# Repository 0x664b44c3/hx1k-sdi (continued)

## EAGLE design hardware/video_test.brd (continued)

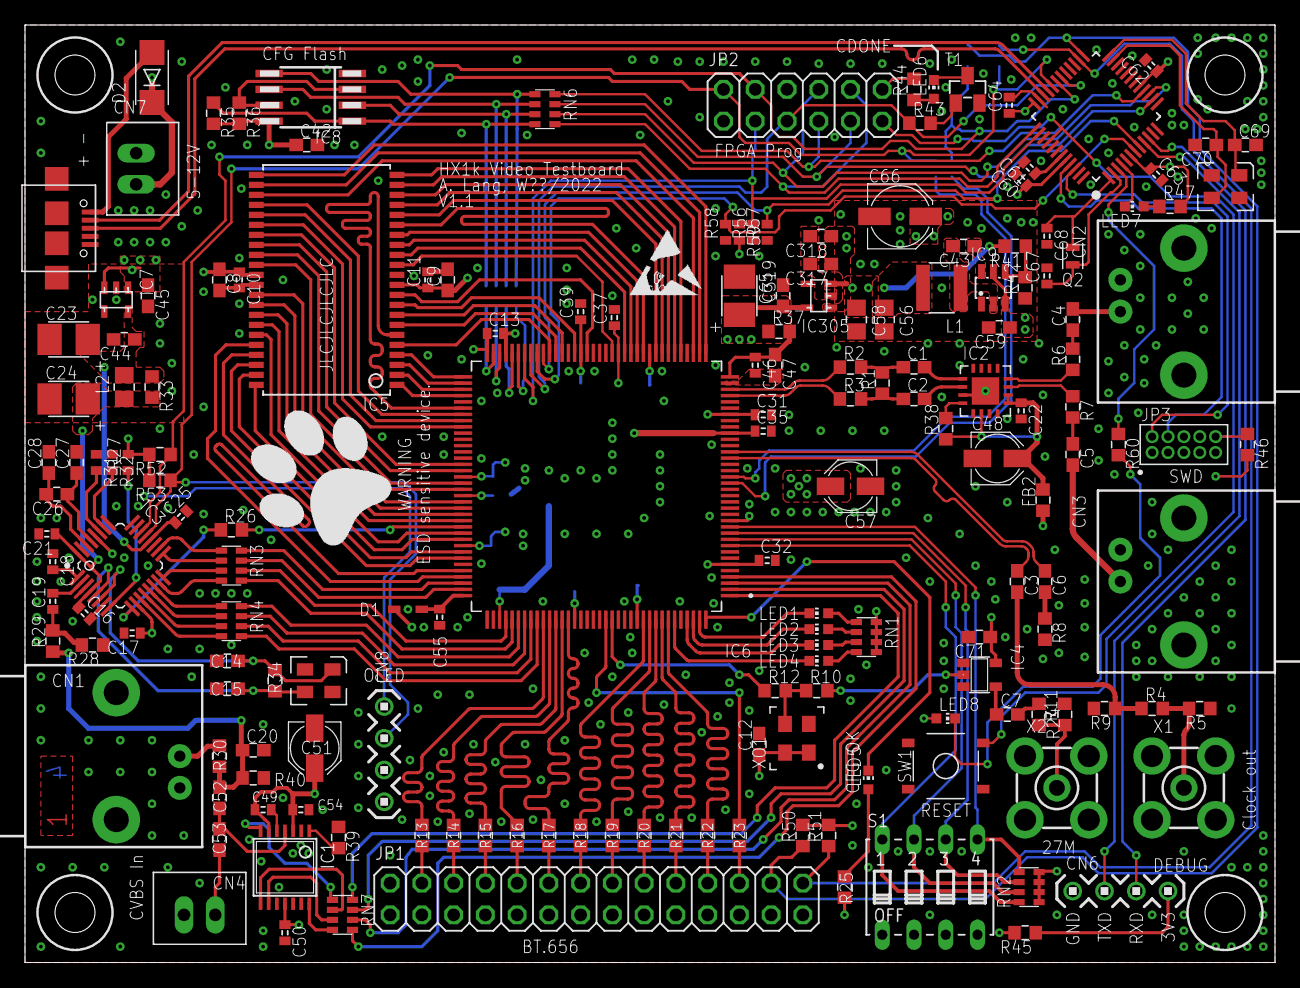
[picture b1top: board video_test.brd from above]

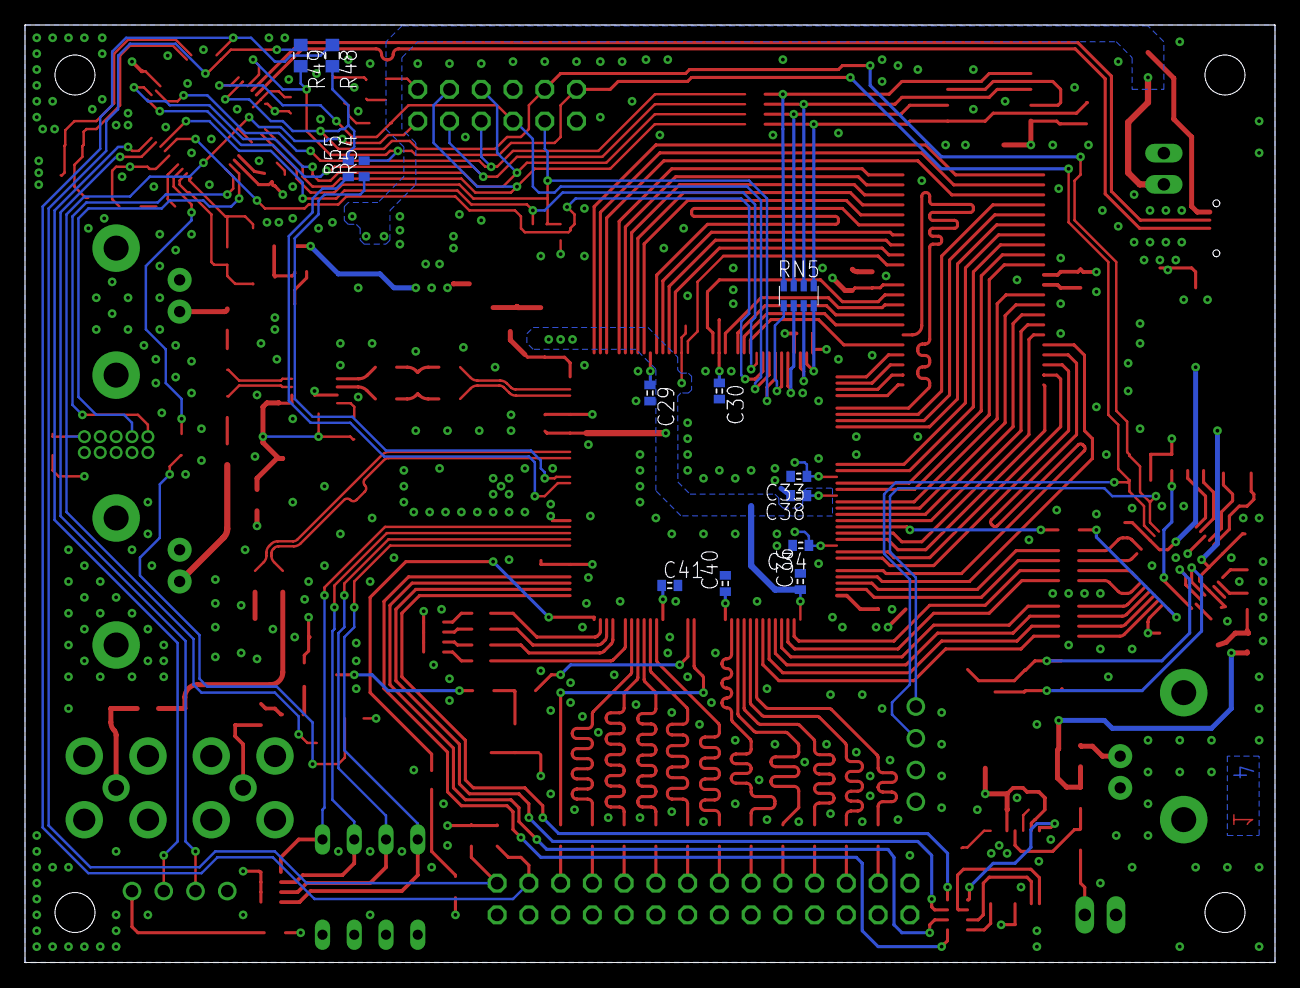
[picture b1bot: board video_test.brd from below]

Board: 4 copper layers, 100.0 x 75.0 mm, 185 parts (13 on the bottom side), 198 nets.

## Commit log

2022-07-05 added hardware source files
2022-07-05 Added schematics pdf and initial fpga bitstream
2022-07-05 added image of the pcb
2022-07-05 Update README.md
    added image
2022-07-05 update schematics pdf (only contained first page)
2022-07-06 added docu images
2022-07-08 better board photo
2022-07-08 Update errata.md
    fixed typo
2022-07-09 Added serializer hdl file
